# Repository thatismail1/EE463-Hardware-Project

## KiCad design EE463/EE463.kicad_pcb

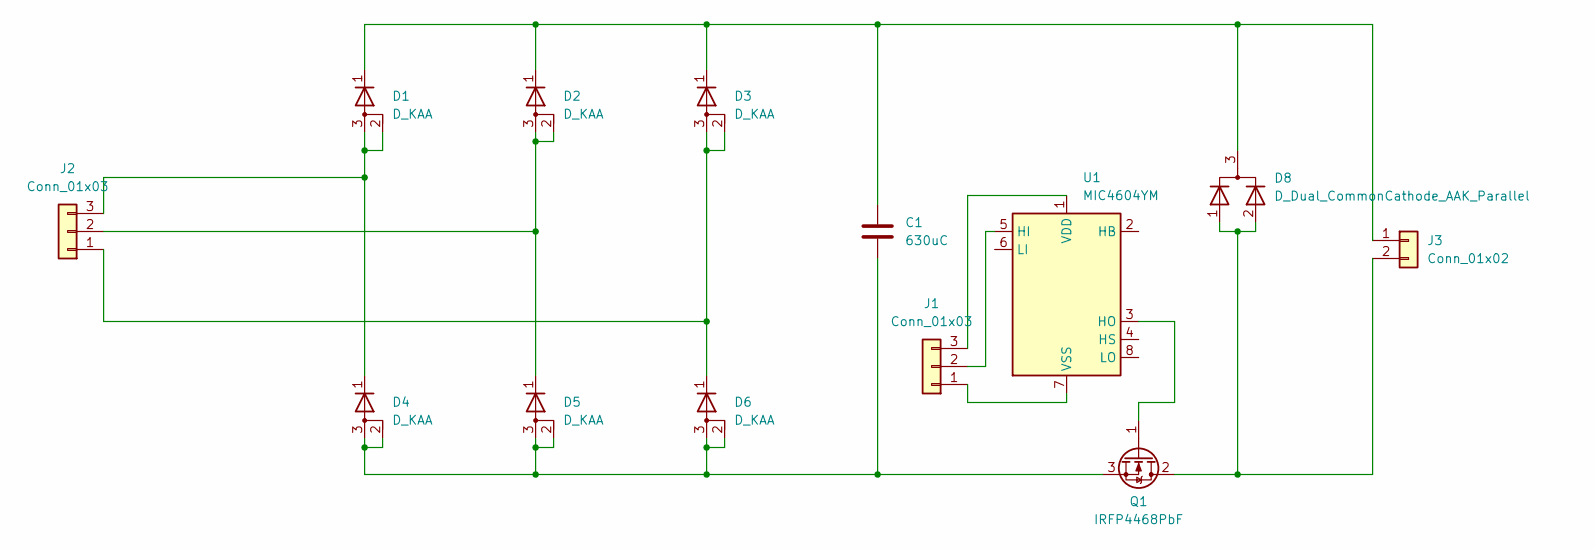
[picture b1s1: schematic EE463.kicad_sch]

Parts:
C1: 630uC; CP_Radial_D24.0mm_P10.00mm_SnapIn
D1, D2, D3, D4, D5, D6: D_KAA; TO-247-3_Vertical
D8: D_Dual_CommonCathode_AAK_Parallel; TO-247-3_Vertical
J1, J2: Conn_01x03; PhoenixContact_MC_1,5_3-G-5.08_1x03_P5.08mm_Horizontal
J3: Conn_01x02; PhoenixContact_MC_1,5_2-G-3.5_1x02_P3.50mm_Horizontal
Q1: IRFP4468PbF; TO-247-3_Vertical
U1: MIC4604YM; SOIC-8_3.9x4.9mm_P1.27mm

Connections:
unnamed: C1.1, D1.1 (K), D2.1 (K), D3.1 (K), D8.3 (K), J3.1
unnamed: D1.2 (A), D1.3 (A), D4.1 (K), J2.3
unnamed: D2.2 (A), D2.3 (A), D5.1 (K), J2.2
unnamed: D3.2 (A), D3.3 (A), D6.1 (K), J2.1
unnamed: J1.1, U1.7 (VSS)
unnamed: J1.2, U1.5 (HI)
unnamed: J1.3, U1.1 (VDD)
unnamed: D8.1 (A), D8.2 (A), J3.2, Q1.2 (D)
unnamed: Q1.1 (G), U1.3 (HO)
unnamed: C1.2, D4.2 (A), D4.3 (A), D5.2 (A), D5.3 (A), D6.2 (A), D6.3 (A), Q1.3 (S)

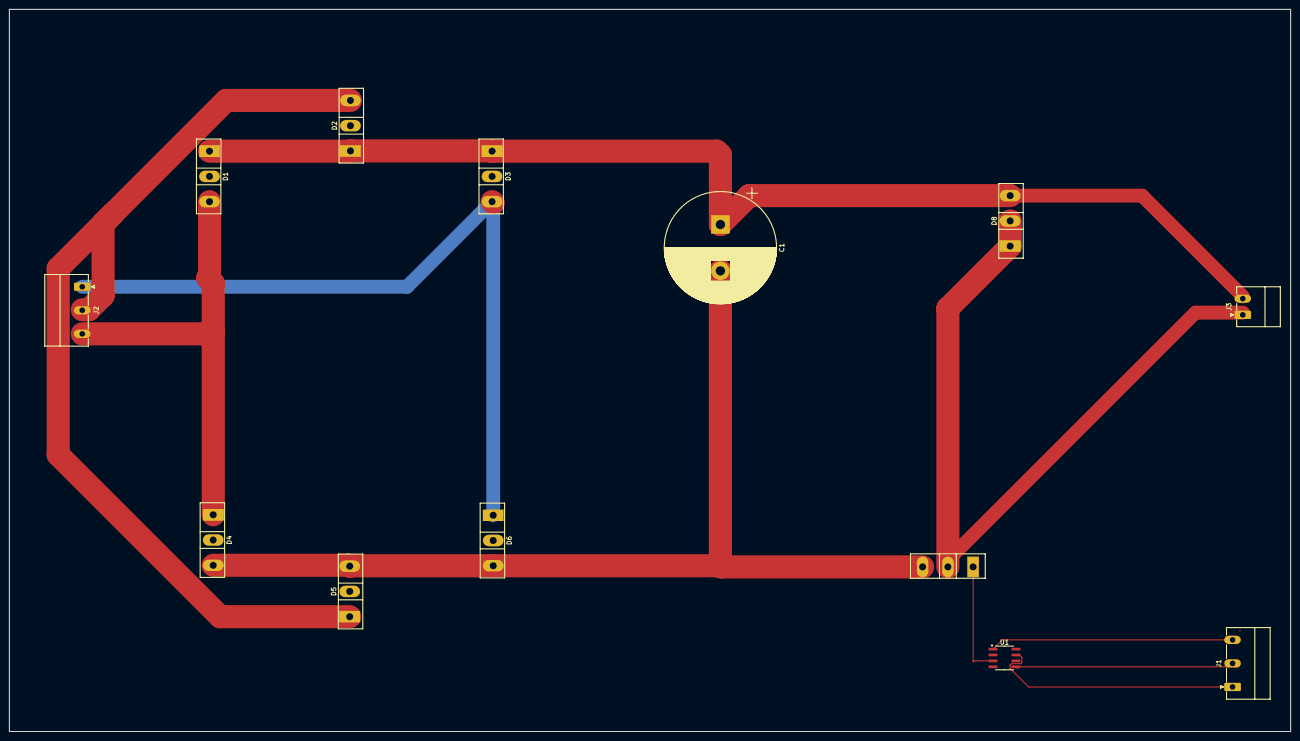
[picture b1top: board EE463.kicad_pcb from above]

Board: 8 copper layers, 276.6 x 155.9 mm, 13 parts (0 on the bottom side), 10 nets.

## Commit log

2024-11-17 simulink diagram of the project
    I tried to build a simulink model of three phase rectifier + buck converter + dc machine
2024-11-23 Updated Project Design
2024-11-26 Final Project Design
2024-11-27 Create Datasheets Page
2024-11-27 Datasheets For The Components We Finalized To Use
2024-11-27 EE463 Project Phase 1 Report
2025-01-18 Create md
2025-01-18 Real Components are added
2025-01-19 added pi controller with soft starting method
2025-01-20 Delete EEE463_HardwareProject_final_design.slx
    fixed
2025-01-20 Create results
2025-01-20 Simulation Plots
2025-01-20 Latest Datasheets We Used In Our Design
2025-01-20 Delete Plots directory
    will be reuploaded with better pics
2025-01-20 Create Plots
2025-01-20 Added Plots With Better Resolution
2025-01-20 Create controller
2025-01-20 Rename controller to controller.c
2025-01-20 Final Version Of Simulink Design
2025-01-20 Gate driver
2025-01-20 Added Heatsink
2025-01-20 KiCad Files
2025-01-20 Final Design In PLECS Enviroment
2025-01-20 Added Final Report
